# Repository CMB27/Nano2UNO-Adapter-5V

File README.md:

# Nano2UNO Adapter 5V

The Nano2UNO Adapter 5V is a circuit board to adapt 5V Arduino Nano boards the the Arduino UNO form factor.

All the IO pins on the Nano2UNO Adapter 5V are wired one to one from the Nano to the UNO form factor, no exceptions.
Pins A6 and A7 of the Nano are not connected because these pins are not present in the UNO form factor.

> [!NOTE]
> This design is distributed WITHOUT ANY EXPRESS OR IMPLIED WARRANTY, INCLUDING OF MERCHANTABILITY, SATISFACTORY QUALITY AND FITNESS FOR A PARTICULAR PURPOSE.

### Compatibility
The Nano2UNO Adapter 5V should, in theory, be compatible with the following Arduino Nano boards:
- [Arduino Nano](https://store.arduino.cc/collections/boards-modules/products/arduino-nano)
- [Arduino Nano Every](https://store.arduino.cc/collections/boards-modules/products/arduino-nano-every)

### Documentation
- [Schematic](Nano2UNO-Adapter-5V.pdf)
- [KiCAD Source Files](src)
- [STEP 3D Model](extras/Nano2UNO-Adapter-5V.step)

## Components

### Circuit Board
#### Specifications
- Board Length: __68.58mm__
- Board Width: __53.34mm__
- Board Thickness: __1.6mm__
- Substrate Material: __FR4__
- Copper Layers: __2__
- Copper Thickness: __1oz__
- Soldermask Color: __Any__ (Blue Suggested)
- Smallest Hole Diameter: __0.8mm__
- Smallest Trace Width: __0.2mm__ (7.8mil)
- Smallest Trace Spacing: __0.2mm__ (7.8mil)

#### Suppliers
Below are some circuit board manufacturers I have used in the past.
Generally you will need to upload the upload the [gerber and drill files](gerbers) to their websites in a .zip folder.

- [OSH Park](https://oshpark.com) is a US based circuit board fabrication service.
  They tend to be more expensive than other manufacturers and the number of options they give you are limited (If you use this manufacturer, I hope you like purple).

- [Seeed Studio Fusion](https://www.seeedstudio.com/fusion_pcb.html) makes circuit boards in China.
  They have a lot of options when ordering; please refer to the [specifications](#specifications) above when making your choices.
  They do have a circuit board assembly service as well, but I am not especially familiar with it.

### Purchase Components

| References | Quantity | Manufacturer | Part Number    | Description                     | Notes                                                                                  |
|------------|---------:|--------------|----------------|---------------------------------|----------------------------------------------------------------------------------------|
| D1         |        1 | Vishay       | SB260S-E3/54   | DO-41 Diode                     | This provides reverse voltage protection on the VIN pin and barrel jack.               |
| J1, J3     |        2 | Samtec       | ESW-108-33-L-S | 1x8 Socket Header               | These are extended socket headers that make up part of the Arduino UNO interface.      |
| J2         |        1 | Samtec       | ESW-110-33-L-S | 1x10 Socket Header              | This is an extended socket header that makes up part of the Arduino UNO interface.     |
| J4         |        1 | Samtec       | ESW-106-33-L-S | 1x6 Socket Header               | This is an extended socket header that makes up part of the Arduino UNO interface.     |
| J5, J6     |        2 | Sullins      | PPPC151LFBN-RC	| 1x15 Socket Header              | These are typical, 8.5mm tall, socket headers that make up the Arduino Nano interface. |
| J7         |        1 | TSW/Samtec   | TSW-103-15-L-D | 2x3 Pin Header                  | This is an extended pin header that makes up part of the Arduino UNO interface.        |
| J8         |        1 | CUI          | PJ-102A        | 2.0mm ID, 5.5mm OD Barrel Jack  | This is a pretty common barrel jack.                                                   |
| SW1        |        1 | TE           | 1825910-6      | 6mm Pushbutton Switch           | This is a generic 6mm pushbutton switch.                                               |

#### Suppliers
Below are some electronics suppliers I have used in the past:

- [Digi-Key](https://www.digikey.com/) is my usual go-to supplier for electronic components.
  Their website makes it pretty easy to sort through parts.

- [Mouser](https://www.mouser.com/) is very similar to Digi-Key in a lot of ways.
  They sometimes have better pricing, and they have excellent customer support.

- [Newark](https://www.newark.com/) tends to have a bit different selection than Digi-Key and Mouser, especially in the area of connectors.

- [Octopart](https://octopart.com/) is not a supplier per se; it is essenitally an electronic component search engine.
  This can be a very helpful tool when looking for parts, especially somewhat unusual ones, like extended socket headers.

All of these suppliers have a feature on their respective websites where you can upload a spreadsheet file, such as [Nano2UNO-Adapter-5V-BOM.csv](Nano2UNO-Adapter-5V-BOM.csv), to populate the cart or find parts.

## Assembly

### Tools and Supplies
| Item              | Optional | Notes                                                                                                                                              |
|-------------------|----------|----------------------------------------------------------------------------------------------------------------------------------------------------|
| Soldering Iron    | No       | Make sure you use a good quality soldering iron. A poor quality soldering iron will give you a miserable soldering experience.                     |
| Flush Cutters     | No       | These are used to trim component leads.                                                                                                            |
| Flux Core Solder  | No       | Leaded solder is easier to work with, but lead-free solder is better for the environment.                                                          |
| Solder Flux       | Yes      | Extra flux will make the solder flow better. I don't usually use it when through-hole soldering, but it can be helpful.                            |
| Solder Wick       | Yes      | This is used to remove solder from places you don't want it.                                                                                       |
| Solder Sucker     | Yes      | If you need to de-solder a component, this, along with solder wick, is the tool you want. This can quickly remove most of the solder from a joint. |
| Arduino Shield    | Yes      | This can be used to hold the stacking socket headers in place while being assembled.                                                               |
| Isopropyl Alcohol | Maybe    | This is used to remove flux. It is not needed if you are using no-clean flux.                                                                      |
| Dish Soap         | Maybe    | This is used to remove flux residue. It is not needed if you are using no-clean flux.                                                              |

> **Note on Flux**  
> Traditional flux if left on the assembled circuit board could cause some serious issues.
> It can potentially cause shorts or significant [parasitic capacitance](https://en.wikipedia.org/wiki/Parasitic_capacitance).
> It is also somewhat corrosive and can, over time, damage your circuit board.
> This sort of flux must be cleaned off the board after assembly.
> 
> To address these issues there are no-clean fluxes, that can be left on the circuit board assembly and are unlikly to cause these issues.
> There are also water-soluble fluxes that can be cleaned off with hot water, though I have found that some isopropyl alcohol can speed up the process.
> There are also fluxes that are both no-clean and water soluble; this is what I like to use.

### Assembly Steps
All the components are placed on the front side of the board and solderd on the back side of the board.
These steps go through soldering each component, starting with the shortest.

> The [interactive HTML BOM](https://github.com/CMB27/Nano2UNO-Adapter-5V/blob/main/extras/Nano2UNO-Adapter-5V-interactive-BOM.html) may be helpful to you in this process.
> It graphically shows where each component goes on the board.
> You will need to download it in order to view it; GitHub does not render HTML files in repositories.

#### 1. D1 (Diode)
- Bend the diode leads so that the part will fit in the footprint.
- Place the diode, ensuring that the side with the line closest to it (the cathode) is facing the squarish pad.
- Bend the diode leads on the backside of the board to ensure the diode remains in place when soldering.
- Solder the leads to the pads.
- Trim the leads using flush cutters.

#### 2. SW1 (Pushbutton Switch)
- Place the switch; it should stay in place.
- Solder the leads to the board.

#### 3. J5-J6 (Arduino Nano Socket)
- If you have an Arduino Nano board, place the socket headers on the Nano's pins, then place the socket header pins through the holes on the Nano2UNO circuit board.
  This will ensure your Nano board will line up with the sockets once they are soldered in place.
  If you do not have an Arduino Nano board on hand, place the socket header pins as precisely as you can.
- Carefully flip the board over the board, holding the socket headers in place.
  This can be difficult; it may be necessary to solder each socket header one at a time.
- Tack solder the end pins of the socket headers.
- Check that the socket headers are straight and seated correctly.
  If necessary remelt the solder joints to adjust the socket headers. (This is where flux can be nice.)
- Once the headers are straight, solder the remaining pins. I usually go every other pin to avoid heat build up, then go back soldering the pins I skipped.
- If you used an Arduino Nano board to place the sockets, remove it now.

#### 4. J8 (Barrel Jack)
- Place the barrel Jack.
- Tack solder the pin near the middle of the component.
- Check that the part is straight and seated correctly.
- Solder the remaining pins.

#### 5. J7 (ICSP Header)
- Place the pin header.
- Tack solder one pin. I like to solder one of the corners.
  Be careful when soldering this component; it has a lot of exposed metal that can burn you when heated by a soldering iron.
- Check that the part is straight and seated correctly.
- Solder the remaining pins.

#### 6. J1-J4 (Arduino UNO Interface)
- If you have a shield for the Arduino UNO, place the socket headers on its pins, then place the socket header pins through the holes on the Nano2UNO circuit board.
  This will make it easier and faster to install the sockets.
  If you don't have a shield you will likely need to install the sockets one at a time.
- Carefully flip the board over the board, holding the socket headers in place.
- Tack solder the end pins of the socket headers.
- Check that the socket headers are straight and seated correctly.
- Once the headers are straight, solder the remaining pins.
- If you used a shield, remove it now.

#### 7. Clean Flux Off Board  
_If you used no-clean flux, you can skip this step._

> [!NOTE]
> This step was written with water-soluble flux in mind.  
> If you used non-water-soluble flux, you may need to use a different cleaning process.

- Use isopropyl alcohol with a toothbrush to remove the bulk of the flux.
- Clean the board with dish soap and warm water using the same toothbrush.
- Dry the board thoroughly. I like to use compressed air for this step.

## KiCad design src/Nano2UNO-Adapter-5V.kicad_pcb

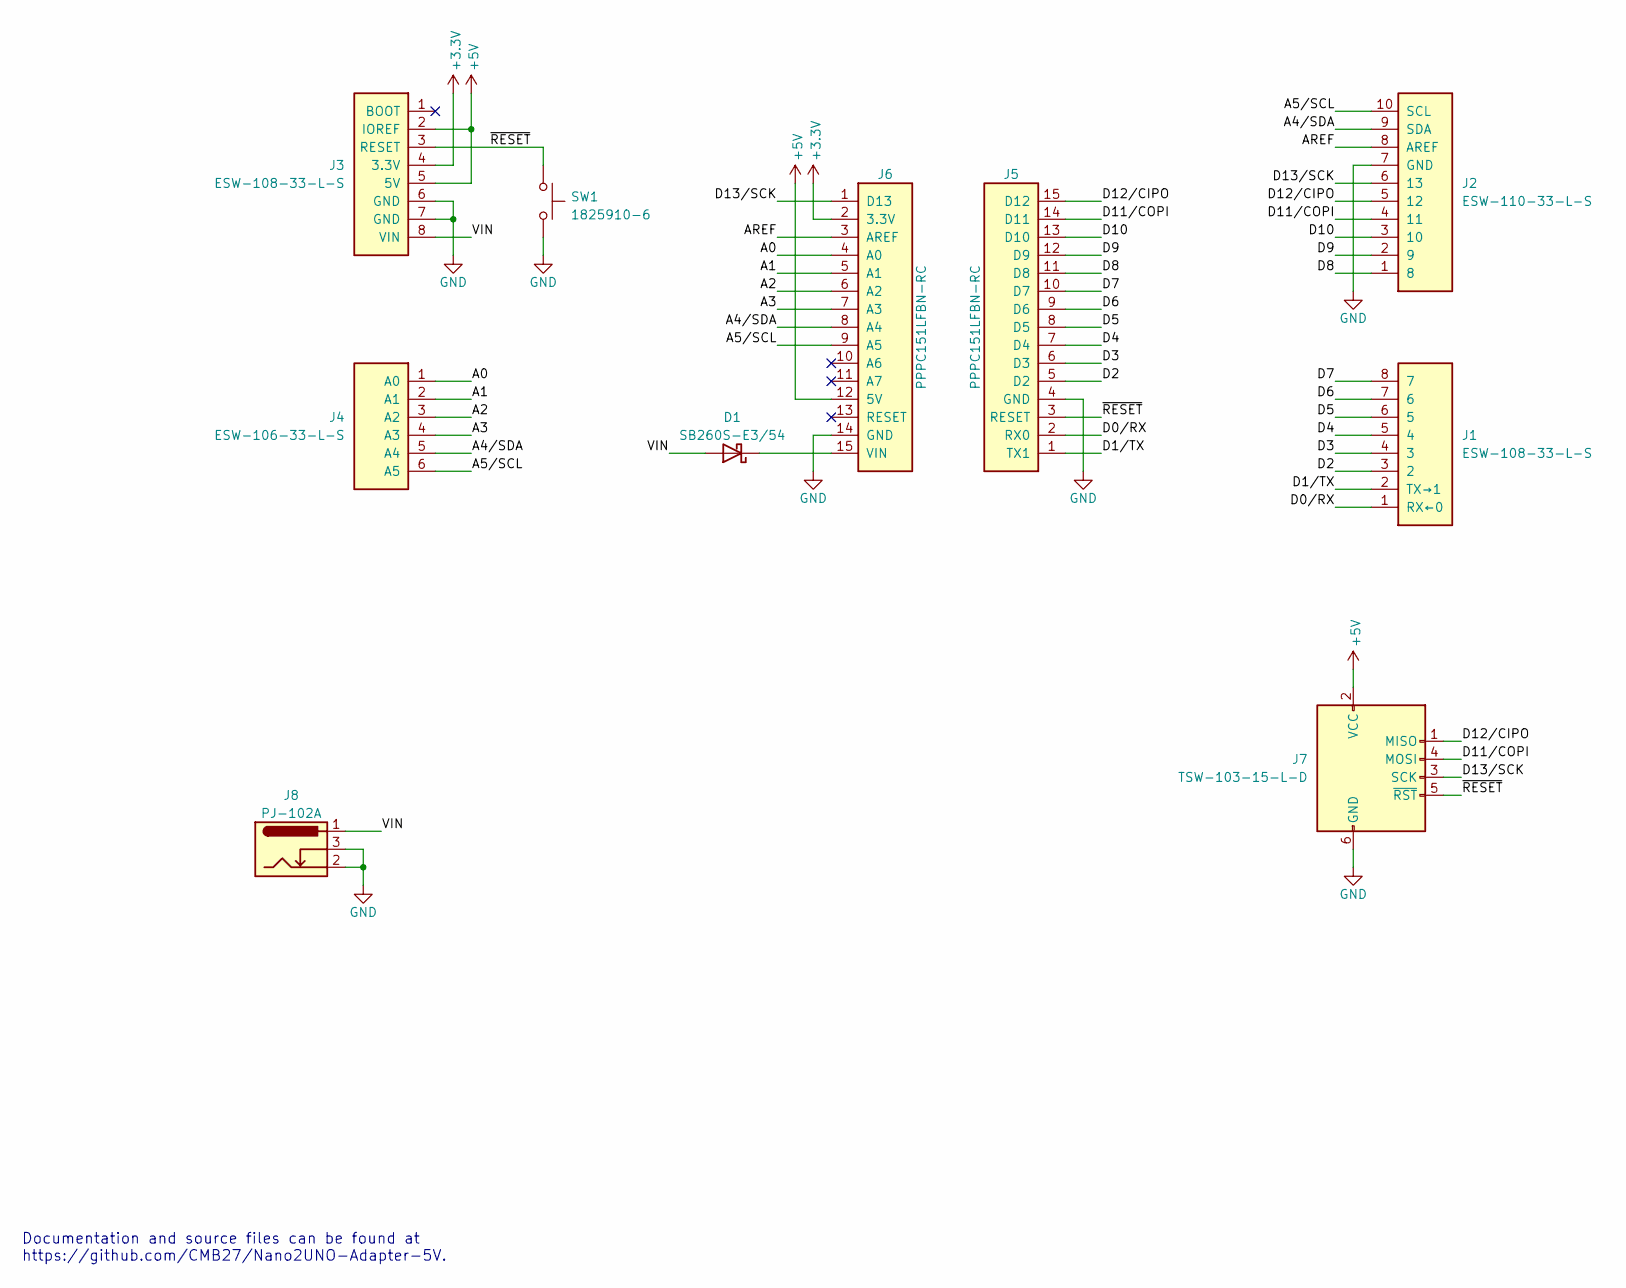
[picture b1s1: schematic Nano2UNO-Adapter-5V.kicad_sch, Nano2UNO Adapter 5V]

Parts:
D1: SB260S-E3/54; D_DO-41_SOD81_P10.16mm_Horizontal; Part Number SB260S-E3/54
J1: ESW-108-33-L-S; PinSocket_1x08_P2.54mm_Vertical_UNO_Digital_1; Part Number ESW-108-33-L-S
J2: ESW-110-33-L-S; PinSocket_1x10_P2.54mm_Vertical_UNO_Digital_2; Part Number ESW-110-33-L-S
J3: ESW-108-33-L-S; PinSocket_1x08_P2.54mm_Vertical_UNO_Power; Part Number ESW-108-33-L-S
J4: ESW-106-33-L-S; PinSocket_1x06_P2.54mm_Vertical_UNO_Analog; Part Number ESW-106-33-L-S
J5: PPPC151LFBN-RC; PinSocket_1x15_P2.54mm_Vertical_Nano_1; Part Number PPPC151LFBN-RC
J6: PPPC151LFBN-RC; PinSocket_1x15_P2.54mm_Vertical_Nano_2; Part Number PPPC151LFBN-RC
J7: TSW-103-15-L-D; PinHeader_2x03_P2.54mm_Vertical_UNO_ICSP; Part Number TSW-103-15-L-D
J8: PJ-102A; BarrelJack_CUI_PJ-102A_Horizontal; Part Number PJ-102A
SW1: 1825910-6; SW_PUSH_6mm_Reset; Part Number 1825910-6

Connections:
+3V3: J3.4 (3.3V), J6.2 (3.3V)
+5V: J3.2 (IOREF), J3.5 (5V), J6.12 (5V), J7.2 (VCC)
/A0: J4.1 (A0), J6.4 (A0)
/A1: J4.2 (A1), J6.5 (A1)
/A2: J4.3 (A2), J6.6 (A2)
/A3: J4.4 (A3), J6.7 (A3)
/A4/SDA: J2.9 (SDA), J4.5 (A4), J6.8 (A4)
/A5/SCL: J2.10 (SCL), J4.6 (A5), J6.9 (A5)
/AREF: J2.8 (AREF), J6.3 (AREF)
/D0/RX: J1.1 (RX←0), J5.2 (RX0)
/D1/TX: J1.2 (TX→1), J5.1 (TX1)
/D2: J1.3 (2), J5.5 (D2)
/D3: J1.4 (3), J5.6 (D3)
/D4: J1.5 (4), J5.7 (D4)
/D5: J1.6 (5), J5.8 (D5)
/D6: J1.7 (6), J5.9 (D6)
/D7: J1.8 (7), J5.10 (D7)
/D8: J2.1 (8), J5.11 (D8)
/D9: J2.2 (9), J5.12 (D9)
/D10: J2.3 (10), J5.13 (D10)
/D11/COPI: J2.4 (11), J5.14 (D11), J7.4 (MOSI)
/D12/CIPO: J2.5 (12), J5.15 (D12), J7.1 (MISO)
/D13/SCK: J2.6 (13), J6.1 (D13), J7.3 (SCK)
/VIN: D1.2 (A), J3.8 (VIN), J8.1
/~RESET: J3.3 (RESET), J5.3 (RESET), J7.5 (~RST), SW1.2
GND: J2.7 (GND), J3.6 (GND), J3.7 (GND), J5.4 (GND), J6.14 (GND), J7.6 (GND), J8.2, J8.3, SW1.1
unnamed: D1.1 (K), J6.15 (VIN)

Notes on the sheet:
Documentation and source files can be found at https://github.com/CMB27/Nano2UNO-Adapter-5V.

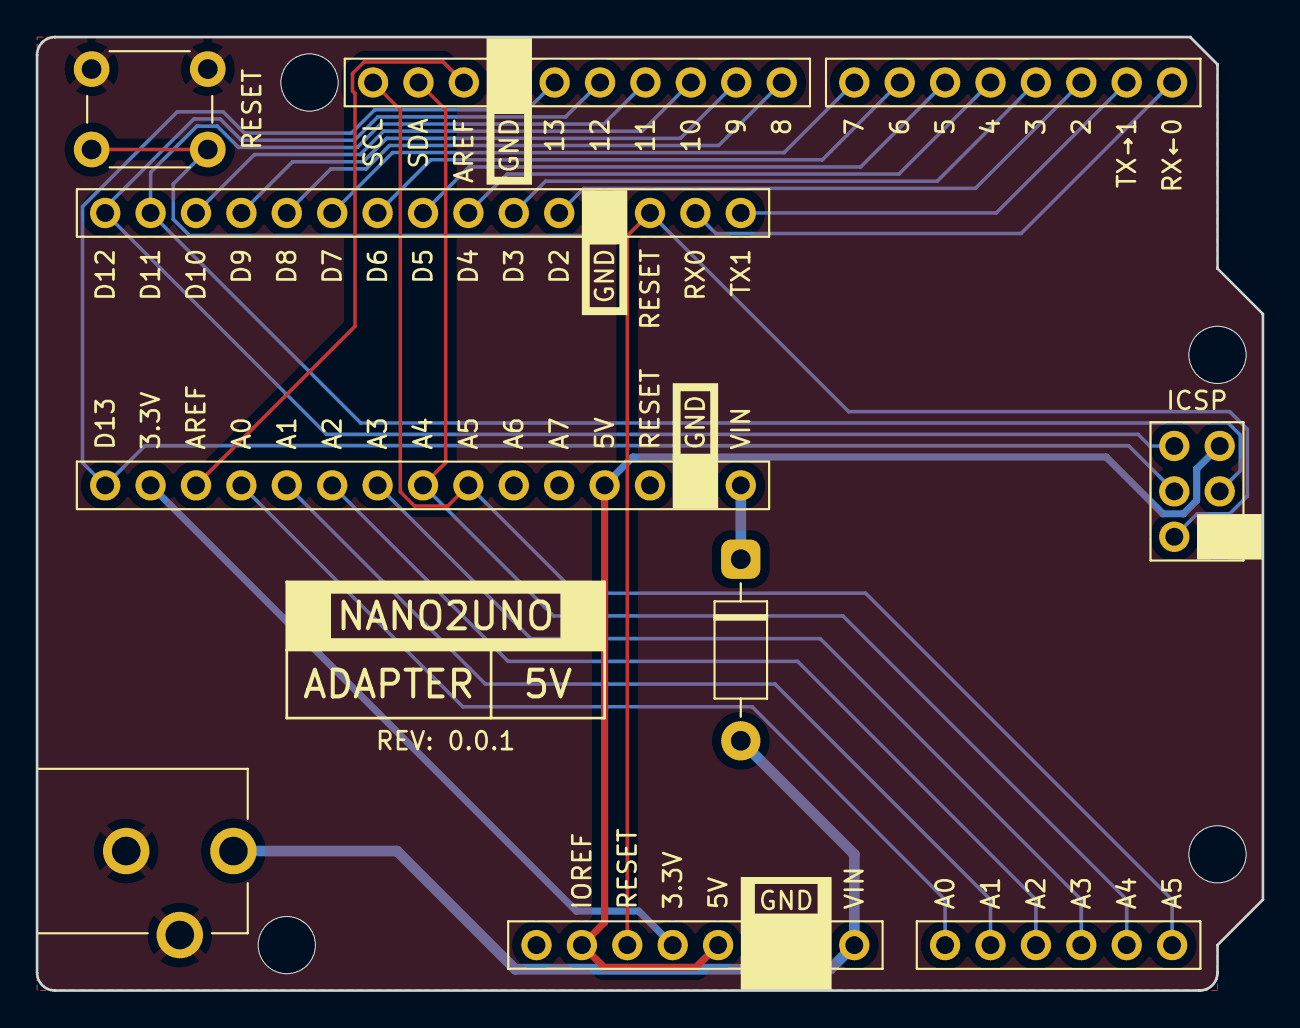
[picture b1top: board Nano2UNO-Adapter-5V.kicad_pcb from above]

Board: 2 copper layers, 68.6 x 53.3 mm, 14 parts (0 on the bottom side), 27 nets.

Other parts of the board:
MH1, MH2, MH3, MH4: MountingHole_3.2mm

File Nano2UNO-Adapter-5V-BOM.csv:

Item,References,Quantity,Manufacturer,Part Number,Description
1,,1,,,Nano2UNO Adapter 5V Bare Circuit Board
2,D1,1,Vishay,SB260S-E3/54,DO-41 Diode
3,"J1, J3",2,Samtec,ESW-108-33-L-S,1x8 Socket Header
4,J2,1,Samtec,ESW-110-33-L-S,1x10 Socket Header
5,J4,1,Samtec,ESW-106-33-L-S,1x6 Socket Header
6,"J5, J6",2,Sullins,PPPC151LFBN-RC,1x15 Socket Header
7,J7,1,TSW/Samtec,TSW-103-15-L-D,2x3 Pin Header
8,J8,1,CUI,PJ-102A,"2.0mm ID, 5.5mm OD Barrel Jack"
9,SW1,1,TE,1825910-6,6mm Pushbutton Switch

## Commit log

2023-12-31 Changed RST to RESET and REF to AREF. Tweaked README and production file creation instructions.

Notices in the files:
src/Nano2UNO-Adapter-5V.kicad_pcb:
© 2023 C. M. Bulliner. Released under the CERN-OHL-P v2 license.
LICENSED UNDER CERN-OHL-P V2
